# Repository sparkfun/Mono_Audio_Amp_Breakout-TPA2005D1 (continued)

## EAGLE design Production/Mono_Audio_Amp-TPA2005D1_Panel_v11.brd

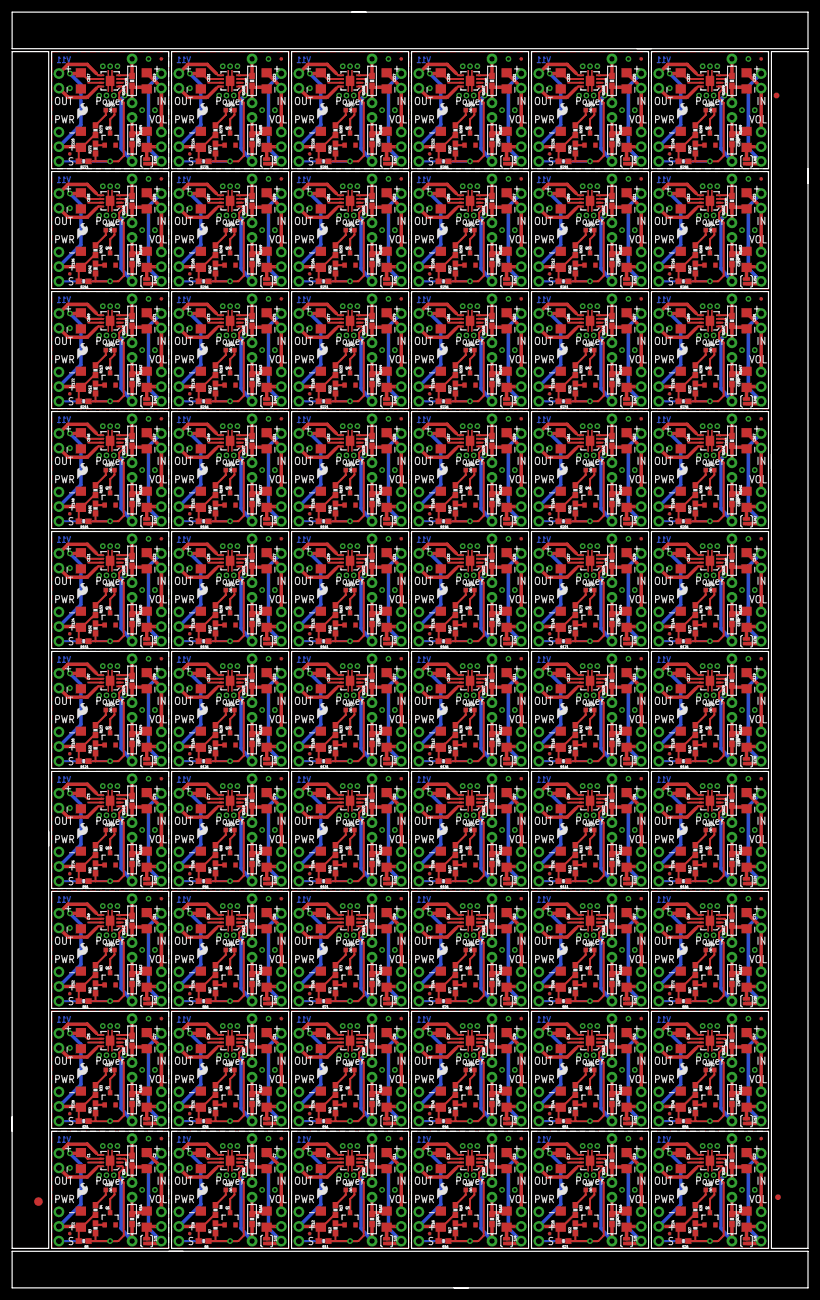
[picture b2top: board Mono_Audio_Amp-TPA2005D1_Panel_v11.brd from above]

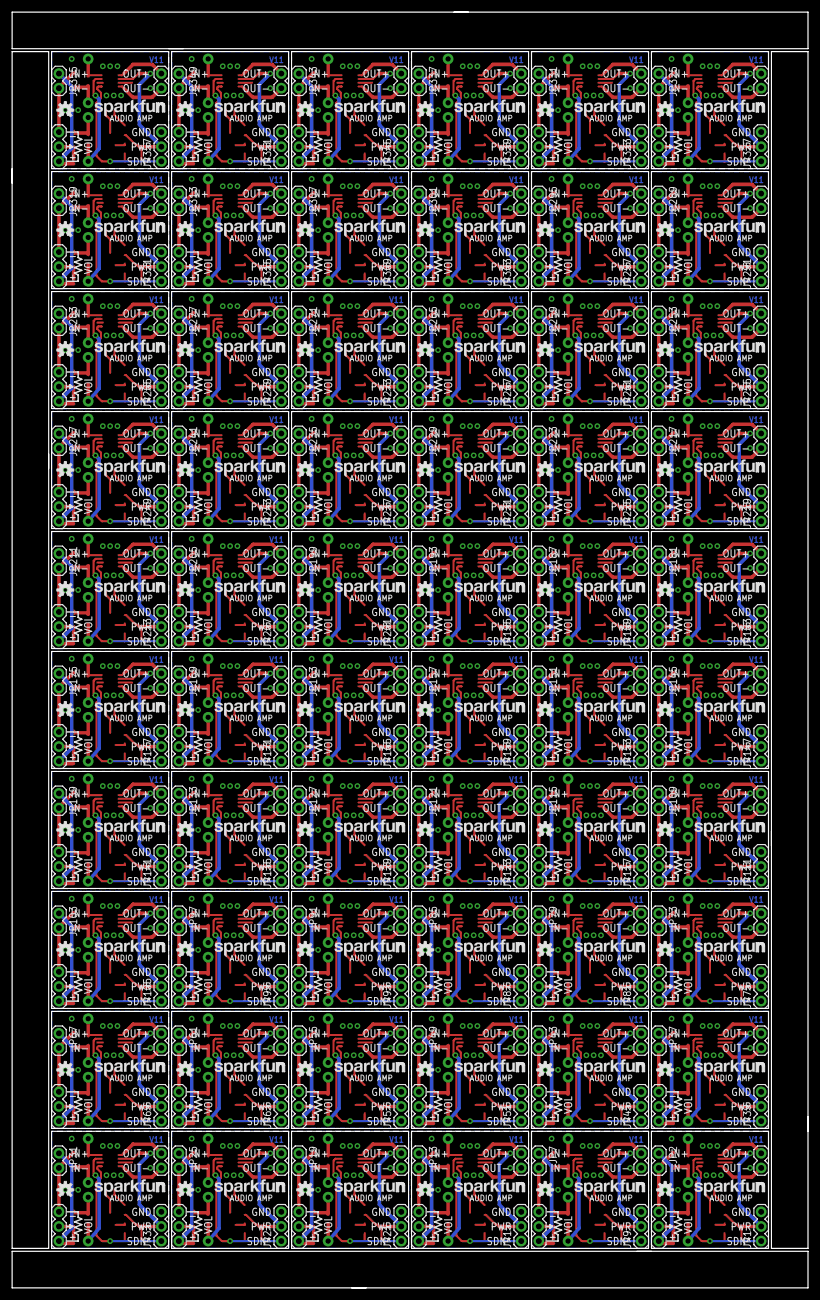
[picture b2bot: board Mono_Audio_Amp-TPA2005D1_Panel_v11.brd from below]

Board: 2 copper layers, 138.2 x 221.5 mm, 1443 parts (360 on the bottom side), 900 nets.

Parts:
C1, C3, C4, C5, C6, C7, C9, C10, C11, C13, C14, C15, C17, C18, C19, C21, C22, C23, C25, C26, C27, C29, C30, C31, C33, C34, C35, C37, C38, C39, C41, C42, C43, C45, C46, C47, C49, C50, C51, C53, C54, C55, C57, C58, C59, C61, C62, C63, C65, C66, C67, C69, C70, C71, C73, C74, C75, C77, C78, C79, C81, C82, C83, C85, C86, C87, C89, C90, C91, C93, C94, C95, C97, C98, C99, C101, C102, C103, C105, C106, C107, C109, C110, C111, C113, C114, C115, C117, C118, C119, C121, C122, C123, C125, C126, C127, C129, C130, C131, C133, C134, C135, C137, C138, C139, C141, C142, C143, C145, C146, C147, C149, C150, C151, C153, C154, C155, C157, C158, C159, C161, C162, C163, C165, C166, C167, C169, C170, C171, C173, C174, C175, C177, C178, C179, C181, C182, C183, C185, C186, C187, C189, C190, C191, C193, C194, C195, C197, C198, C199, C201, C202, C203, C205, C206, C207, C209, C210, C211, C213, C214, C215, C217, C218, C219, C221, C222, C223, C225, C226, C227, C229, C230, C231, C233, C234, C235, C237, C238, C239: 1uF; 1206
C2, C8, C12, C16, C20, C24, C28, C32, C36, C40, C44, C48, C52, C56, C60, C64, C68, C72, C76, C80, C84, C88, C92, C96, C100, C104, C108, C112, C116, C120, C124, C128, C132, C136, C140, C144, C148, C152, C156, C160, C164, C168, C172, C176, C180, C184, C188, C192, C196, C200, C204, C208, C212, C216, C220, C224, C228, C232, C236, C240: 10uF; 1206
E$1: FIDUCIAL-1.5X3
E$2, E$5: FIDUCIAL-1X2
JP1, JP9, JP15, JP21, JP27, JP33, JP39, JP45, JP51, JP57, JP63, JP69, JP75, JP81, JP87, JP93, JP99, JP105, JP111, JP117, JP123, JP129, JP135, JP141, JP147, JP153, JP159, JP165, JP171, JP177, JP183, JP189, JP195, JP201, JP207, JP213, JP219, JP225, JP231, JP237, JP243, JP249, JP255, JP261, JP267, JP273, JP279, JP285, JP291, JP297, JP303, JP309, JP315, JP321, JP327, JP333, JP339, JP345, JP351, JP357: POWER; 1X03
JP2, JP7, JP13, JP19, JP25, JP31, JP37, JP43, JP49, JP55, JP61, JP67, JP73, JP79, JP85, JP91, JP97, JP103, JP109, JP115, JP121, JP127, JP133, JP139, JP145, JP151, JP157, JP163, JP169, JP175, JP181, JP187, JP193, JP199, JP205, JP211, JP217, JP223, JP229, JP235, JP241, JP247, JP253, JP259, JP265, JP271, JP277, JP283, JP289, JP295, JP301, JP307, JP313, JP319, JP325, JP331, JP337, JP343, JP349, JP355: IN; 1X02
JP3, JP8, JP14, JP20, JP26, JP32, JP38, JP44, JP50, JP56, JP62, JP68, JP74, JP80, JP86, JP92, JP98, JP104, JP110, JP116, JP122, JP128, JP134, JP140, JP146, JP152, JP158, JP164, JP170, JP176, JP182, JP188, JP194, JP200, JP206, JP212, JP218, JP224, JP230, JP236, JP242, JP248, JP254, JP260, JP266, JP272, JP278, JP284, JP290, JP296, JP302, JP308, JP314, JP320, JP326, JP332, JP338, JP344, JP350, JP356: OUT; 1X02
JP4, JP10, JP16, JP22, JP28, JP34, JP40, JP46, JP52, JP58, JP64, JP70, JP76, JP82, JP88, JP94, JP100, JP106, JP112, JP118, JP124, JP130, JP136, JP142, JP148, JP154, JP160, JP166, JP172, JP178, JP184, JP190, JP196, JP202, JP208, JP214, JP220, JP226, JP232, JP238, JP244, JP250, JP256, JP262, JP268, JP274, JP280, JP286, JP292, JP298, JP304, JP310, JP316, JP322, JP328, JP334, JP340, JP346, JP352, JP358: VOLUME; 1X03
JP5, JP6, JP11, JP12, JP17, JP18, JP23, JP24, JP29, JP30, JP35, JP36, JP41, JP42, JP47, JP48, JP53, JP54, JP59, JP60, JP65, JP66, JP71, JP72, JP77, JP78, JP83, JP84, JP89, JP90, JP95, JP96, JP101, JP102, JP107, JP108, JP113, JP114, JP119, JP120, JP125, JP126, JP131, JP132, JP137, JP138, JP143, JP144, JP149, JP150, JP155, JP156, JP161, JP162, JP167, JP168, JP173, JP174, JP179, JP180, JP185, JP186, JP191, JP192, JP197, JP198, JP203, JP204, JP209, JP210, JP215, JP216, JP221, JP222, JP227, JP228, JP233, JP234, JP239, JP240, JP245, JP246, JP251, JP252, JP257, JP258, JP263, JP264, JP269, JP270, JP275, JP276, JP281, JP282, JP287, JP288, JP293, JP294, JP299, JP300, JP305, JP306, JP311, JP312, JP317, JP318, JP323, JP324, JP329, JP330, JP335, JP336, JP341, JP342, JP347, JP348, JP353, JP354, JP359, JP360: FIDUCIALUFIDUCIAL; MICRO-FIDUCIAL
LED1, LED2, LED3, LED4, LED5, LED6, LED7, LED8, LED9, LED10, LED11, LED12, LED13, LED14, LED15, LED16, LED17, LED18, LED19, LED20, LED21, LED22, LED23, LED24, LED25, LED26, LED27, LED28, LED29, LED30, LED31, LED32, LED33, LED34, LED35, LED36, LED37, LED38, LED39, LED40, LED41, LED42, LED43, LED44, LED45, LED46, LED47, LED48, LED49, LED50, LED51, LED52, LED53, LED54, LED55, LED56, LED57, LED58, LED59, LED60: LED-0603
LOGO1, LOGO3, LOGO5, LOGO7, LOGO9, LOGO11, LOGO13, LOGO15, LOGO17, LOGO19, LOGO21, LOGO23, LOGO25, LOGO27, LOGO29, LOGO31, LOGO33, LOGO35, LOGO37, LOGO39, LOGO41, LOGO43, LOGO45, LOGO47, LOGO49, LOGO51, LOGO53, LOGO55, LOGO57, LOGO59, LOGO61, LOGO63, LOGO65, LOGO67, LOGO69, LOGO71, LOGO73, LOGO75, LOGO77, LOGO79, LOGO81, LOGO83, LOGO85, LOGO87, LOGO89, LOGO91, LOGO93, LOGO95, LOGO97, LOGO99, LOGO101, LOGO103, LOGO105, LOGO107, LOGO109, LOGO111, LOGO113, LOGO115, LOGO117, LOGO119: LOGO-SFENW2; SFE-NEW-WEB
LOGO2, LOGO4, LOGO6, LOGO8, LOGO10, LOGO12, LOGO14, LOGO16, LOGO18, LOGO20, LOGO22, LOGO24, LOGO26, LOGO28, LOGO30, LOGO32, LOGO34, LOGO36, LOGO38, LOGO40, LOGO42, LOGO44, LOGO46, LOGO48, LOGO50, LOGO52, LOGO54, LOGO56, LOGO58, LOGO60, LOGO62, LOGO64, LOGO66, LOGO68, LOGO70, LOGO72, LOGO74, LOGO76, LOGO78, LOGO80, LOGO82, LOGO84, LOGO86, LOGO88, LOGO90, LOGO92, LOGO94, LOGO96, LOGO98, LOGO100, LOGO102, LOGO104, LOGO106, LOGO108, LOGO110, LOGO112, LOGO114, LOGO116, LOGO118, LOGO120: LOGO-SFESK; SFE-LOGO-FLAME
Q1, Q2, Q3, Q4, Q5, Q6, Q7, Q8, Q9, Q10, Q11, Q12, Q13, Q14, Q15, Q16, Q17, Q18, Q19, Q20, Q21, Q22, Q23, Q24, Q25, Q26, Q27, Q28, Q29, Q30, Q31, Q32, Q33, Q34, Q35, Q36, Q37, Q38, Q39, Q40, Q41, Q42, Q43, Q44, Q45, Q46, Q47, Q48, Q49, Q50, Q51, Q52, Q53, Q54, Q55, Q56, Q57, Q58, Q59, Q60: MMBT2222A; SOT23-3
R1, R2, R9, R10, R14, R15, R19, R20, R24, R25, R29, R30, R34, R35, R39, R40, R44, R45, R49, R50, R54, R55, R59, R60, R64, R65, R69, R70, R74, R75, R79, R80, R84, R85, R89, R90, R94, R95, R99, R100, R104, R105, R109, R110, R114, R115, R119, R120, R124, R125, R129, R130, R134, R135, R139, R140, R144, R145, R149, R150, R154, R155, R159, R160, R164, R165, R169, R170, R174, R175, R179, R180, R184, R185, R189, R190, R194, R195, R199, R200, R204, R205, R209, R210, R214, R215, R219, R220, R224, R225, R229, R230, R234, R235, R239, R240, R244, R245, R249, R250, R254, R255, R259, R260, R264, R265, R269, R270, R274, R275, R279, R280, R284, R285, R289, R290, R294, R295, R299, R300: 150K; 0603-RES
R1A, R1A1, R1A2, R1A3, R1A4, R1A5, R1A6, R1A7, R1A8, R1A9, R1A10, R1A11, R1A12, R1A13, R1A14, R1A15, R1A16, R1A17, R1A18, R1A19, R1A20, R1A21, R1A22, R1A23, R1A24, R1A25, R1A26, R1A27, R1A28, R1A29, R1A30, R1A31, R1A32, R1A33, R1A34, R1A35, R1A36, R1A37, R1A38, R1A39, R1A40, R1A41, R1A42, R1A43, R1A44, R1A45, R1A46, R1A47, R1A48, R1A49, R1A50, R1A51, R1A52, R1A53, R1A54, R1A55, R1A56, R1A57, R1A58, R1A59, R2A, R2A1, R2A2, R2A3, R2A4, R2A5, R2A6, R2A7, R2A8, R2A9, R2A10, R2A11, R2A12, R2A13, R2A14, R2A15, R2A16, R2A17, R2A18, R2A19, R2A20, R2A21, R2A22, R2A23, R2A24, R2A25, R2A26, R2A27, R2A28, R2A29, R2A30, R2A31, R2A32, R2A33, R2A34, R2A35, R2A36, R2A37, R2A38, R2A39, R2A40, R2A41, R2A42, R2A43, R2A44, R2A45, R2A46, R2A47, R2A48, R2A49, R2A50, R2A51, R2A52, R2A53, R2A54, R2A55, R2A56, R2A57, R2A58, R2A59: DNP; AXIAL-0.3
R3, R5, R6, R7, R11, R12, R16, R17, R21, R22, R26, R27, R31, R32, R36, R37, R41, R42, R46, R47, R51, R52, R56, R57, R61, R62, R66, R67, R71, R72, R76, R77, R81, R82, R86, R87, R91, R92, R96, R97, R101, R102, R106, R107, R111, R112, R116, R117, R121, R122, R126, R127, R131, R132, R136, R137, R141, R142, R146, R147, R151, R152, R156, R157, R161, R162, R166, R167, R171, R172, R176, R177, R181, R182, R186, R187, R191, R192, R196, R197, R201, R202, R206, R207, R211, R212, R216, R217, R221, R222, R226, R227, R231, R232, R236, R237, R241, R242, R246, R247, R251, R252, R256, R257, R261, R262, R266, R267, R271, R272, R276, R277, R281, R282, R286, R287, R291, R292, R296, R297: 10K; 0603-RES
R4, R8, R13, R18, R23, R28, R33, R38, R43, R48, R53, R58, R63, R68, R73, R78, R83, R88, R93, R98, R103, R108, R113, R118, R123, R128, R133, R138, R143, R148, R153, R158, R163, R168, R173, R178, R183, R188, R193, R198, R203, R208, R213, R218, R223, R228, R233, R238, R243, R248, R253, R258, R263, R268, R273, R278, R283, R288, R293, R298: 330; 0603-RES
SJ1, SJ2, SJ3, SJ4, SJ5, SJ6, SJ7, SJ8, SJ9, SJ10, SJ11, SJ12, SJ13, SJ14, SJ15, SJ16, SJ17, SJ18, SJ19, SJ20, SJ21, SJ22, SJ23, SJ24, SJ25, SJ26, SJ27, SJ28, SJ29, SJ30, SJ31, SJ32, SJ33, SJ34, SJ35, SJ36, SJ37, SJ38, SJ39, SJ40, SJ41, SJ42, SJ43, SJ44, SJ45, SJ46, SJ47, SJ48, SJ49, SJ50, SJ51, SJ52, SJ53, SJ54, SJ55, SJ56, SJ57, SJ58, SJ59, SJ60: SJ_2S-NOTRACE
U1, U2, U3, U4, U5, U6, U7, U8, U9, U10, U11, U12, U13, U14, U15, U16, U17, U18, U19, U20, U21, U22, U23, U24, U25, U26, U27, U28, U29, U30, U31, U32, U33, U34, U35, U36, U37, U38, U39, U40, U41, U42, U43, U44, U45, U46, U47, U48, U49, U50, U51, U52, U53, U54, U55, U56, U57, U58, U59, U60: TPA2005D1DRB; QFN-8_PAD
U$1, U$2, U$3, U$4, U$5, U$6, U$7, U$8, U$9, U$10, U$11, U$12, U$13, U$14, U$15, U$16, U$17, U$18, U$19, U$20, U$21, U$22, U$23, U$24, U$25, U$26, U$27, U$28, U$29, U$30, U$31, U$32, U$33, U$34, U$35, U$36, U$37, U$38, U$39, U$40, U$41, U$42, U$43, U$44, U$45, U$46, U$47, U$48, U$49, U$50, U$51, U$52, U$53, U$54, U$55, U$56, U$57, U$58, U$59, U$60: OSHW-LOGOS; OSHW-LOGO-S

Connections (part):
GND: C1.2, C2.2, JP1.3, Q1.2, U1.7, U1.10, U1.11, U1.12, U1.13
GND1: C5.2, C8.2, JP9.3, Q2.2, U2.7, U2.10, U2.11, U2.12, U2.13
GND2: C9.2, C12.2, JP15.3, Q3.2, U3.7, U3.10, U3.11, U3.12, U3.13
GND3: C13.2, C16.2, JP21.3, Q4.2, U4.7, U4.10, U4.11, U4.12, U4.13
GND4: C17.2, C20.2, JP27.3, Q5.2, U5.7, U5.10, U5.11, U5.12, U5.13
GND5: C21.2, C24.2, JP33.3, Q6.2, U6.7, U6.10, U6.11, U6.12, U6.13
GND6: C25.2, C28.2, JP39.3, Q7.2, U7.7, U7.10, U7.11, U7.12, U7.13
GND7: C29.2, C32.2, JP45.3, Q8.2, U8.7, U8.10, U8.11, U8.12, U8.13
GND8: C33.2, C36.2, JP51.3, Q9.2, U9.7, U9.10, U9.11, U9.12, U9.13
GND9: C37.2, C40.2, JP57.3, Q10.2, U10.7, U10.10, U10.11, U10.12, U10.13
GND10: C41.2, C44.2, JP63.3, Q11.2, U11.7, U11.10, U11.11, U11.12, U11.13
GND11: C45.2, C48.2, JP69.3, Q12.2, U12.7, U12.10, U12.11, U12.12, U12.13
GND12: C49.2, C52.2, JP75.3, Q13.2, U13.7, U13.10, U13.11, U13.12, U13.13
GND13: C53.2, C56.2, JP81.3, Q14.2, U14.7, U14.10, U14.11, U14.12, U14.13
GND14: C57.2, C60.2, JP87.3, Q15.2, U15.7, U15.10, U15.11, U15.12, U15.13
GND15: C61.2, C64.2, JP93.3, Q16.2, U16.7, U16.10, U16.11, U16.12, U16.13
GND16: C65.2, C68.2, JP99.3, Q17.2, U17.7, U17.10, U17.11, U17.12, U17.13
GND17: C69.2, C72.2, JP105.3, Q18.2, U18.7, U18.10, U18.11, U18.12, U18.13
GND18: C73.2, C76.2, JP111.3, Q19.2, U19.7, U19.10, U19.11, U19.12, U19.13
GND19: C77.2, C80.2, JP117.3, Q20.2, U20.7, U20.10, U20.11, U20.12, U20.13
GND20: C81.2, C84.2, JP123.3, Q21.2, U21.7, U21.10, U21.11, U21.12, U21.13
GND21: C85.2, C88.2, JP129.3, Q22.2, U22.7, U22.10, U22.11, U22.12, U22.13
GND22: C89.2, C92.2, JP135.3, Q23.2, U23.7, U23.10, U23.11, U23.12, U23.13
GND23: C93.2, C96.2, JP141.3, Q24.2, U24.7, U24.10, U24.11, U24.12, U24.13
GND24: C97.2, C100.2, JP147.3, Q25.2, U25.7, U25.10, U25.11, U25.12, U25.13
GND25: C101.2, C104.2, JP153.3, Q26.2, U26.7, U26.10, U26.11, U26.12, U26.13
GND26: C105.2, C108.2, JP159.3, Q27.2, U27.7, U27.10, U27.11, U27.12, U27.13
GND27: C109.2, C112.2, JP165.3, Q28.2, U28.7, U28.10, U28.11, U28.12, U28.13
GND28: C113.2, C116.2, JP171.3, Q29.2, U29.7, U29.10, U29.11, U29.12, U29.13
GND29: C117.2, C120.2, JP177.3, Q30.2, U30.7, U30.10, U30.11, U30.12, U30.13
GND30: C121.2, C124.2, JP183.3, Q31.2, U31.7, U31.10, U31.11, U31.12, U31.13
GND31: C125.2, C128.2, JP189.3, Q32.2, U32.7, U32.10, U32.11, U32.12, U32.13
GND32: C129.2, C132.2, JP195.3, Q33.2, U33.7, U33.10, U33.11, U33.12, U33.13
GND33: C133.2, C136.2, JP201.3, Q34.2, U34.7, U34.10, U34.11, U34.12, U34.13
GND34: C137.2, C140.2, JP207.3, Q35.2, U35.7, U35.10, U35.11, U35.12, U35.13
GND35: C141.2, C144.2, JP213.3, Q36.2, U36.7, U36.10, U36.11, U36.12, U36.13
GND36: C145.2, C148.2, JP219.3, Q37.2, U37.7, U37.10, U37.11, U37.12, U37.13
GND37: C149.2, C152.2, JP225.3, Q38.2, U38.7, U38.10, U38.11, U38.12, U38.13
GND38: C153.2, C156.2, JP231.3, Q39.2, U39.7, U39.10, U39.11, U39.12, U39.13
GND39: C157.2, C160.2, JP237.3, Q40.2, U40.7, U40.10, U40.11, U40.12, U40.13
GND40: C161.2, C164.2, JP243.3, Q41.2, U41.7, U41.10, U41.11, U41.12, U41.13
GND41: C165.2, C168.2, JP249.3, Q42.2, U42.7, U42.10, U42.11, U42.12, U42.13
GND42: C169.2, C172.2, JP255.3, Q43.2, U43.7, U43.10, U43.11, U43.12, U43.13
GND43: C173.2, C176.2, JP261.3, Q44.2, U44.7, U44.10, U44.11, U44.12, U44.13
GND44: C177.2, C180.2, JP267.3, Q45.2, U45.7, U45.10, U45.11, U45.12, U45.13
GND45: C181.2, C184.2, JP273.3, Q46.2, U46.7, U46.10, U46.11, U46.12, U46.13
GND46: C185.2, C188.2, JP279.3, Q47.2, U47.7, U47.10, U47.11, U47.12, U47.13
GND47: C189.2, C192.2, JP285.3, Q48.2, U48.7, U48.10, U48.11, U48.12, U48.13
GND48: C193.2, C196.2, JP291.3, Q49.2, U49.7, U49.10, U49.11, U49.12, U49.13
GND49: C197.2, C200.2, JP297.3, Q50.2, U50.7, U50.10, U50.11, U50.12, U50.13
GND50: C201.2, C204.2, JP303.3, Q51.2, U51.7, U51.10, U51.11, U51.12, U51.13
GND51: C205.2, C208.2, JP309.3, Q52.2, U52.7, U52.10, U52.11, U52.12, U52.13
GND52: C209.2, C212.2, JP315.3, Q53.2, U53.7, U53.10, U53.11, U53.12, U53.13
GND53: C213.2, C216.2, JP321.3, Q54.2, U54.7, U54.10, U54.11, U54.12, U54.13
GND54: C217.2, C220.2, JP327.3, Q55.2, U55.7, U55.10, U55.11, U55.12, U55.13
GND55: C221.2, C224.2, JP333.3, Q56.2, U56.7, U56.10, U56.11, U56.12, U56.13
GND56: C225.2, C228.2, JP339.3, Q57.2, U57.7, U57.10, U57.11, U57.12, U57.13
GND57: C229.2, C232.2, JP345.3, Q58.2, U58.7, U58.10, U58.11, U58.12, U58.13
GND58: C233.2, C236.2, JP351.3, Q59.2, U59.7, U59.10, U59.11, U59.12, U59.13
GND59: C237.2, C240.2, JP357.3, Q60.2, U60.7, U60.10, U60.11, U60.12, U60.13
IN+: JP2.1, JP4.1, SJ1.2
IN+1: JP7.1, JP10.1, SJ2.2
IN+2: JP13.1, JP16.1, SJ3.2
IN+3: JP19.1, JP22.1, SJ4.2
IN+4: JP25.1, JP28.1, SJ5.2
IN+5: JP31.1, JP34.1, SJ6.2
IN+6: JP37.1, JP40.1, SJ7.2
IN+7: JP43.1, JP46.1, SJ8.2
IN+8: JP49.1, JP52.1, SJ9.2
IN+9: JP55.1, JP58.1, SJ10.2
IN+10: JP61.1, JP64.1, SJ11.2
IN+11: JP67.1, JP70.1, SJ12.2
IN+12: JP73.1, JP76.1, SJ13.2
IN+13: JP79.1, JP82.1, SJ14.2
IN+14: JP85.1, JP88.1, SJ15.2
IN+15: JP91.1, JP94.1, SJ16.2
IN+16: JP97.1, JP100.1, SJ17.2
IN+17: JP103.1, JP106.1, SJ18.2
IN+18: JP109.1, JP112.1, SJ19.2
IN+19: JP115.1, JP118.1, SJ20.2
IN+20: JP121.1, JP124.1, SJ21.2
IN+21: JP127.1, JP130.1, SJ22.2
IN+22: JP133.1, JP136.1, SJ23.2
IN+23: JP139.1, JP142.1, SJ24.2
IN+24: JP145.1, JP148.1, SJ25.2
IN+25: JP151.1, JP154.1, SJ26.2
IN+26: JP157.1, JP160.1, SJ27.2
IN+27: JP163.1, JP166.1, SJ28.2
IN+28: JP169.1, JP172.1, SJ29.2
IN+29: JP175.1, JP178.1, SJ30.2
IN+30: JP181.1, JP184.1, SJ31.2
IN+31: JP187.1, JP190.1, SJ32.2
IN+32: JP193.1, JP196.1, SJ33.2
IN+33: JP199.1, JP202.1, SJ34.2
IN+34: JP205.1, JP208.1, SJ35.2
IN+35: JP211.1, JP214.1, SJ36.2
IN+36: JP217.1, JP220.1, SJ37.2
IN+37: JP223.1, JP226.1, SJ38.2
IN+38: JP229.1, JP232.1, SJ39.2
IN+39: JP235.1, JP238.1, SJ40.2
IN+40: JP241.1, JP244.1, SJ41.2
IN+41: JP247.1, JP250.1, SJ42.2
IN+42: JP253.1, JP256.1, SJ43.2
IN+43: JP259.1, JP262.1, SJ44.2
IN+44: JP265.1, JP268.1, SJ45.2
IN+45: JP271.1, JP274.1, SJ46.2
IN+46: JP277.1, JP280.1, SJ47.2
IN+47: JP283.1, JP286.1, SJ48.2
IN+48: JP289.1, JP292.1, SJ49.2
IN+49: JP295.1, JP298.1, SJ50.2
IN+50: JP301.1, JP304.1, SJ51.2
IN+51: JP307.1, JP310.1, SJ52.2
IN+52: JP313.1, JP316.1, SJ53.2
IN+53: JP319.1, JP322.1, SJ54.2
IN+54: JP325.1, JP328.1, SJ55.2
IN+55: JP331.1, JP334.1, SJ56.2
IN+56: JP337.1, JP340.1, SJ57.2
IN+57: JP343.1, JP346.1, SJ58.2
IN+58: JP349.1, JP352.1, SJ59.2
IN+59: JP355.1, JP358.1, SJ60.2
IN+AMP: R1.2, R1A.P$2, U1.3
IN+AMP1: R1A1.P$2, R9.2, U2.3
IN+AMP2: R1A2.P$2, R14.2, U3.3
IN+AMP3: R1A3.P$2, R19.2, U4.3
IN+AMP4: R1A4.P$2, R24.2, U5.3
IN+AMP5: R1A5.P$2, R29.2, U6.3
IN+AMP6: R1A6.P$2, R34.2, U7.3
IN+AMP7: R1A7.P$2, R39.2, U8.3
IN+AMP8: R1A8.P$2, R44.2, U9.3
IN+AMP9: R1A9.P$2, R49.2, U10.3
IN+AMP10: R1A10.P$2, R54.2, U11.3
IN+AMP11: R1A11.P$2, R59.2, U12.3
IN+AMP12: R1A12.P$2, R64.2, U13.3
IN+AMP13: R1A13.P$2, R69.2, U14.3
IN+AMP14: R1A14.P$2, R74.2, U15.3
IN+AMP15: R1A15.P$2, R79.2, U16.3
IN+AMP16: R1A16.P$2, R84.2, U17.3
IN+AMP17: R1A17.P$2, R89.2, U18.3
IN+AMP18: R1A18.P$2, R94.2, U19.3
IN+AMP19: R1A19.P$2, R99.2, U20.3
IN+AMP20: R1A20.P$2, R104.2, U21.3
IN+AMP21: R1A21.P$2, R109.2, U22.3
IN+AMP22: R1A22.P$2, R114.2, U23.3
IN+AMP23: R1A23.P$2, R119.2, U24.3
IN+AMP24: R1A24.P$2, R124.2, U25.3
IN+AMP25: R1A25.P$2, R129.2, U26.3
IN+AMP26: R1A26.P$2, R134.2, U27.3
IN+AMP27: R1A27.P$2, R139.2, U28.3
IN+AMP28: R1A28.P$2, R144.2, U29.3
IN+AMP29: R1A29.P$2, R149.2, U30.3
IN+AMP30: R1A30.P$2, R154.2, U31.3
IN+AMP31: R1A31.P$2, R159.2, U32.3
IN+AMP32: R1A32.P$2, R164.2, U33.3
IN+AMP33: R1A33.P$2, R169.2, U34.3
IN+AMP34: R1A34.P$2, R174.2, U35.3
IN+AMP35: R1A35.P$2, R179.2, U36.3
IN+AMP36: R1A36.P$2, R184.2, U37.3
IN+AMP37: R1A37.P$2, R189.2, U38.3
IN+AMP38: R1A38.P$2, R194.2, U39.3
IN+AMP39: R1A39.P$2, R199.2, U40.3
IN+AMP40: R1A40.P$2, R204.2, U41.3
IN+AMP41: R1A41.P$2, R209.2, U42.3
IN+AMP42: R1A42.P$2, R214.2, U43.3
IN+AMP43: R1A43.P$2, R219.2, U44.3
IN+AMP44: R1A44.P$2, R224.2, U45.3
IN+AMP45: R1A45.P$2, R229.2, U46.3
IN+AMP46: R1A46.P$2, R234.2, U47.3
IN+AMP47: R1A47.P$2, R239.2, U48.3
IN+AMP48: R1A48.P$2, R244.2, U49.3
IN+AMP49: R1A49.P$2, R249.2, U50.3
IN+AMP50: R1A50.P$2, R254.2, U51.3
IN+AMP51: R1A51.P$2, R259.2, U52.3
IN+AMP52: R1A52.P$2, R264.2, U53.3
IN+AMP53: R1A53.P$2, R269.2, U54.3
IN+AMP54: R1A54.P$2, R274.2, U55.3
IN+AMP55: R1A55.P$2, R279.2, U56.3
IN+AMP56: R1A56.P$2, R284.2, U57.3
IN+AMP57: R1A57.P$2, R289.2, U58.3
IN+AMP58: R1A58.P$2, R294.2, U59.3
IN+AMP59: R1A59.P$2, R299.2, U60.3
IN-: C3.1, JP2.2, JP4.3
IN-1: C7.1, JP7.2, JP10.3
IN-2: C11.1, JP13.2, JP16.3
IN-3: C15.1, JP19.2, JP22.3
IN-4: C19.1, JP25.2, JP28.3
IN-5: C23.1, JP31.2, JP34.3
IN-6: C27.1, JP37.2, JP40.3
IN-7: C31.1, JP43.2, JP46.3
IN-8: C35.1, JP49.2, JP52.3
IN-9: C39.1, JP55.2, JP58.3
IN-10: C43.1, JP61.2, JP64.3
IN-11: C47.1, JP67.2, JP70.3
IN-12: C51.1, JP73.2, JP76.3
IN-13: C55.1, JP79.2, JP82.3
IN-14: C59.1, JP85.2, JP88.3
IN-15: C63.1, JP91.2, JP94.3
IN-16: C67.1, JP97.2, JP100.3
IN-17: C71.1, JP103.2, JP106.3
IN-18: C75.1, JP109.2, JP112.3
IN-19: C79.1, JP115.2, JP118.3
IN-20: C83.1, JP121.2, JP124.3
IN-21: C87.1, JP127.2, JP130.3
IN-22: C91.1, JP133.2, JP136.3
IN-23: C95.1, JP139.2, JP142.3
IN-24: C99.1, JP145.2, JP148.3
IN-25: C103.1, JP151.2, JP154.3
IN-26: C107.1, JP157.2, JP160.3
IN-27: C111.1, JP163.2, JP166.3
IN-28: C115.1, JP169.2, JP172.3
IN-29: C119.1, JP175.2, JP178.3
IN-30: C123.1, JP181.2, JP184.3
IN-31: C127.1, JP187.2, JP190.3
IN-32: C131.1, JP193.2, JP196.3
IN-33: C135.1, JP199.2, JP202.3
IN-34: C139.1, JP205.2, JP208.3
IN-35: C143.1, JP211.2, JP214.3
IN-36: C147.1, JP217.2, JP220.3
IN-37: C151.1, JP223.2, JP226.3
IN-38: C155.1, JP229.2, JP232.3
IN-39: C159.1, JP235.2, JP238.3
IN-40: C163.1, JP241.2, JP244.3
IN-41: C167.1, JP247.2, JP250.3
IN-42: C171.1, JP253.2, JP256.3
IN-43: C175.1, JP259.2, JP262.3
IN-44: C179.1, JP265.2, JP268.3
IN-45: C183.1, JP271.2, JP274.3
IN-46: C187.1, JP277.2, JP280.3
IN-47: C191.1, JP283.2, JP286.3
IN-48: C195.1, JP289.2, JP292.3
IN-49: C199.1, JP295.2, JP298.3
IN-50: C203.1, JP301.2, JP304.3
IN-51: C207.1, JP307.2, JP310.3
IN-52: C211.1, JP313.2, JP316.3
IN-53: C215.1, JP319.2, JP322.3
IN-54: C219.1, JP325.2, JP328.3
IN-55: C223.1, JP331.2, JP334.3
IN-56: C227.1, JP337.2, JP340.3
IN-57: C231.1, JP343.2, JP346.3
IN-58: C235.1, JP349.2, JP352.3
IN-59: C239.1, JP355.2, JP358.3
IN-AMP: R2.2, R2A.P$2, U1.4
IN-AMP1: R2A1.P$2, R10.2, U2.4
IN-AMP2: R2A2.P$2, R15.2, U3.4
IN-AMP3: R2A3.P$2, R20.2, U4.4
IN-AMP4: R2A4.P$2, R25.2, U5.4
IN-AMP5: R2A5.P$2, R30.2, U6.4
IN-AMP6: R2A6.P$2, R35.2, U7.4
IN-AMP7: R2A7.P$2, R40.2, U8.4
IN-AMP8: R2A8.P$2, R45.2, U9.4
IN-AMP9: R2A9.P$2, R50.2, U10.4
IN-AMP10: R2A10.P$2, R55.2, U11.4
IN-AMP11: R2A11.P$2, R60.2, U12.4
IN-AMP12: R2A12.P$2, R65.2, U13.4
IN-AMP13: R2A13.P$2, R70.2, U14.4
IN-AMP14: R2A14.P$2, R75.2, U15.4
IN-AMP15: R2A15.P$2, R80.2, U16.4
IN-AMP16: R2A16.P$2, R85.2, U17.4
IN-AMP17: R2A17.P$2, R90.2, U18.4
IN-AMP18: R2A18.P$2, R95.2, U19.4
IN-AMP19: R2A19.P$2, R100.2, U20.4
IN-AMP20: R2A20.P$2, R105.2, U21.4
IN-AMP21: R2A21.P$2, R110.2, U22.4
IN-AMP22: R2A22.P$2, R115.2, U23.4
IN-AMP23: R2A23.P$2, R120.2, U24.4
IN-AMP24: R2A24.P$2, R125.2, U25.4
IN-AMP25: R2A25.P$2, R130.2, U26.4
IN-AMP26: R2A26.P$2, R135.2, U27.4
IN-AMP27: R2A27.P$2, R140.2, U28.4
IN-AMP28: R2A28.P$2, R145.2, U29.4
IN-AMP29: R2A29.P$2, R150.2, U30.4
IN-AMP30: R2A30.P$2, R155.2, U31.4
IN-AMP31: R2A31.P$2, R160.2, U32.4
IN-AMP32: R2A32.P$2, R165.2, U33.4
IN-AMP33: R2A33.P$2, R170.2, U34.4
IN-AMP34: R2A34.P$2, R175.2, U35.4
IN-AMP35: R2A35.P$2, R180.2, U36.4
IN-AMP36: R2A36.P$2, R185.2, U37.4
IN-AMP37: R2A37.P$2, R190.2, U38.4
IN-AMP38: R2A38.P$2, R195.2, U39.4
IN-AMP39: R2A39.P$2, R200.2, U40.4
IN-AMP40: R2A40.P$2, R205.2, U41.4
IN-AMP41: R2A41.P$2, R210.2, U42.4
IN-AMP42: R2A42.P$2, R215.2, U43.4
IN-AMP43: R2A43.P$2, R220.2, U44.4
IN-AMP44: R2A44.P$2, R225.2, U45.4
IN-AMP45: R2A45.P$2, R230.2, U46.4
IN-AMP46: R2A46.P$2, R235.2, U47.4
IN-AMP47: R2A47.P$2, R240.2, U48.4
IN-AMP48: R2A48.P$2, R245.2, U49.4
IN-AMP49: R2A49.P$2, R250.2, U50.4
IN-AMP50: R2A50.P$2, R255.2, U51.4
IN-AMP51: R2A51.P$2, R260.2, U52.4
IN-AMP52: R2A52.P$2, R265.2, U53.4
IN-AMP53: R2A53.P$2, R270.2, U54.4
IN-AMP54: R2A54.P$2, R275.2, U55.4
IN-AMP55: R2A55.P$2, R280.2, U56.4
IN-AMP56: R2A56.P$2, R285.2, U57.4
IN-AMP57: R2A57.P$2, R290.2, U58.4
IN-AMP58: R2A58.P$2, R295.2, U59.4
IN-AMP59: R2A59.P$2, R300.2, U60.4
unnamed: C4.1, JP4.2, SJ1.1
unnamed: C4.2, R1.1, R1A.P$1
unnamed: C3.2, R2.1, R2A.P$1
unnamed: C6.1, JP10.2, SJ2.1
unnamed: LED2.A, R8.1
unnamed: Q2.1, R7.2
unnamed: LED1.C, Q1.3
unnamed: LED1.A, R4.1
unnamed: Q1.1, R3.2
unnamed: LED2.C, Q2.3
unnamed: C6.2, R1A1.P$1, R9.1
unnamed: C7.2, R2A1.P$1, R10.1
unnamed: C10.1, JP16.2, SJ3.1
unnamed: LED3.A, R13.1
unnamed: Q3.1, R12.2
unnamed: LED3.C, Q3.3
unnamed: C10.2, R1A2.P$1, R14.1
unnamed: C11.2, R2A2.P$1, R15.1
unnamed: C14.1, JP22.2, SJ4.1
unnamed: LED4.A, R18.1
unnamed: Q4.1, R17.2
unnamed: LED4.C, Q4.3
unnamed: C14.2, R1A3.P$1, R19.1
unnamed: C15.2, R2A3.P$1, R20.1
unnamed: C18.1, JP28.2, SJ5.1
unnamed: LED5.A, R23.1
unnamed: Q5.1, R22.2
unnamed: LED5.C, Q5.3
unnamed: C18.2, R1A4.P$1, R24.1
unnamed: C19.2, R2A4.P$1, R25.1
unnamed: C22.1, JP34.2, SJ6.1
unnamed: LED6.A, R28.1
unnamed: Q6.1, R27.2
unnamed: LED6.C, Q6.3
unnamed: C22.2, R1A5.P$1, R29.1
unnamed: C23.2, R2A5.P$1, R30.1
unnamed: C26.1, JP40.2, SJ7.1
unnamed: LED7.A, R33.1
unnamed: Q7.1, R32.2
unnamed: LED7.C, Q7.3
unnamed: C26.2, R1A6.P$1, R34.1
unnamed: C27.2, R2A6.P$1, R35.1
unnamed: C30.1, JP46.2, SJ8.1
unnamed: LED8.A, R38.1
unnamed: Q8.1, R37.2
unnamed: LED8.C, Q8.3
unnamed: C30.2, R1A7.P$1, R39.1
unnamed: C31.2, R2A7.P$1, R40.1
unnamed: C34.1, JP52.2, SJ9.1
unnamed: LED9.A, R43.1
unnamed: Q9.1, R42.2
unnamed: LED9.C, Q9.3
unnamed: C34.2, R1A8.P$1, R44.1
unnamed: C35.2, R2A8.P$1, R45.1
unnamed: C38.1, JP58.2, SJ10.1
unnamed: LED10.A, R48.1
unnamed: Q10.1, R47.2
unnamed: LED10.C, Q10.3
unnamed: C38.2, R1A9.P$1, R49.1
unnamed: C39.2, R2A9.P$1, R50.1
unnamed: C42.1, JP64.2, SJ11.1
unnamed: LED11.A, R53.1
unnamed: Q11.1, R52.2
unnamed: LED11.C, Q11.3
unnamed: C42.2, R1A10.P$1, R54.1
unnamed: C43.2, R2A10.P$1, R55.1
unnamed: C46.1, JP70.2, SJ12.1
unnamed: LED12.A, R58.1
unnamed: Q12.1, R57.2
unnamed: LED12.C, Q12.3
unnamed: C46.2, R1A11.P$1, R59.1
unnamed: C47.2, R2A11.P$1, R60.1
unnamed: C50.1, JP76.2, SJ13.1
unnamed: LED13.A, R63.1
unnamed: Q13.1, R62.2
unnamed: LED13.C, Q13.3
unnamed: C50.2, R1A12.P$1, R64.1
unnamed: C51.2, R2A12.P$1, R65.1
unnamed: C54.1, JP82.2, SJ14.1
unnamed: LED14.A, R68.1
unnamed: Q14.1, R67.2
unnamed: LED14.C, Q14.3
unnamed: C54.2, R1A13.P$1, R69.1
unnamed: C55.2, R2A13.P$1, R70.1
unnamed: C58.1, JP88.2, SJ15.1
unnamed: LED15.A, R73.1
unnamed: Q15.1, R72.2
unnamed: LED15.C, Q15.3
unnamed: C58.2, R1A14.P$1, R74.1
unnamed: C59.2, R2A14.P$1, R75.1
unnamed: C62.1, JP94.2, SJ16.1
unnamed: LED16.A, R78.1
unnamed: Q16.1, R77.2
unnamed: LED16.C, Q16.3
unnamed: C62.2, R1A15.P$1, R79.1
unnamed: C63.2, R2A15.P$1, R80.1
unnamed: C66.1, JP100.2, SJ17.1
unnamed: LED17.A, R83.1
unnamed: Q17.1, R82.2
unnamed: LED17.C, Q17.3
unnamed: C66.2, R1A16.P$1, R84.1
unnamed: C67.2, R2A16.P$1, R85.1
unnamed: C70.1, JP106.2, SJ18.1
unnamed: LED18.A, R88.1
unnamed: Q18.1, R87.2
unnamed: LED18.C, Q18.3
unnamed: C70.2, R1A17.P$1, R89.1
unnamed: C71.2, R2A17.P$1, R90.1
unnamed: C74.1, JP112.2, SJ19.1
unnamed: LED19.A, R93.1
unnamed: Q19.1, R92.2
unnamed: LED19.C, Q19.3
unnamed: C74.2, R1A18.P$1, R94.1
unnamed: C75.2, R2A18.P$1, R95.1
unnamed: C78.1, JP118.2, SJ20.1
unnamed: LED20.A, R98.1
unnamed: Q20.1, R97.2
unnamed: LED20.C, Q20.3
unnamed: C78.2, R1A19.P$1, R99.1
unnamed: C79.2, R2A19.P$1, R100.1
unnamed: C82.1, JP124.2, SJ21.1
unnamed: LED21.A, R103.1
unnamed: Q21.1, R102.2
unnamed: LED21.C, Q21.3
unnamed: C82.2, R1A20.P$1, R104.1
unnamed: C83.2, R2A20.P$1, R105.1
unnamed: C86.1, JP130.2, SJ22.1
unnamed: LED22.A, R108.1
unnamed: Q22.1, R107.2
unnamed: LED22.C, Q22.3
unnamed: C86.2, R1A21.P$1, R109.1
unnamed: C87.2, R2A21.P$1, R110.1
unnamed: C90.1, JP136.2, SJ23.1
unnamed: LED23.A, R113.1
unnamed: Q23.1, R112.2
unnamed: LED23.C, Q23.3
unnamed: C90.2, R1A22.P$1, R114.1
unnamed: C91.2, R2A22.P$1, R115.1
unnamed: C94.1, JP142.2, SJ24.1
unnamed: LED24.A, R118.1
unnamed: Q24.1, R117.2
unnamed: LED24.C, Q24.3
unnamed: C94.2, R1A23.P$1, R119.1
unnamed: C95.2, R2A23.P$1, R120.1
unnamed: C98.1, JP148.2, SJ25.1
unnamed: LED25.A, R123.1
unnamed: Q25.1, R122.2
unnamed: LED25.C, Q25.3
unnamed: C98.2, R1A24.P$1, R124.1
unnamed: C99.2, R2A24.P$1, R125.1
unnamed: C102.1, JP154.2, SJ26.1
unnamed: LED26.A, R128.1
unnamed: Q26.1, R127.2
unnamed: LED26.C, Q26.3
unnamed: C102.2, R1A25.P$1, R129.1
unnamed: C103.2, R2A25.P$1, R130.1
unnamed: C106.1, JP160.2, SJ27.1
unnamed: LED27.A, R133.1
unnamed: Q27.1, R132.2
unnamed: LED27.C, Q27.3
unnamed: C106.2, R1A26.P$1, R134.1
unnamed: C107.2, R2A26.P$1, R135.1
unnamed: C110.1, JP166.2, SJ28.1
unnamed: LED28.A, R138.1
unnamed: Q28.1, R137.2
unnamed: LED28.C, Q28.3
unnamed: C110.2, R1A27.P$1, R139.1
unnamed: C111.2, R2A27.P$1, R140.1
unnamed: C114.1, JP172.2, SJ29.1
unnamed: LED29.A, R143.1
unnamed: Q29.1, R142.2
unnamed: LED29.C, Q29.3
unnamed: C114.2, R1A28.P$1, R144.1
unnamed: C115.2, R2A28.P$1, R145.1
unnamed: C118.1, JP178.2, SJ30.1
unnamed: LED30.A, R148.1
unnamed: Q30.1, R147.2
unnamed: LED30.C, Q30.3
unnamed: C118.2, R1A29.P$1, R149.1
unnamed: C119.2, R2A29.P$1, R150.1
unnamed: C122.1, JP184.2, SJ31.1
unnamed: LED31.A, R153.1
unnamed: Q31.1, R152.2
unnamed: LED31.C, Q31.3
unnamed: C122.2, R1A30.P$1, R154.1
unnamed: C123.2, R2A30.P$1, R155.1
unnamed: C126.1, JP190.2, SJ32.1
unnamed: LED32.A, R158.1
unnamed: Q32.1, R157.2
unnamed: LED32.C, Q32.3
unnamed: C126.2, R1A31.P$1, R159.1
unnamed: C127.2, R2A31.P$1, R160.1
unnamed: C130.1, JP196.2, SJ33.1
unnamed: LED33.A, R163.1
unnamed: Q33.1, R162.2
unnamed: LED33.C, Q33.3
unnamed: C130.2, R1A32.P$1, R164.1
unnamed: C131.2, R2A32.P$1, R165.1
unnamed: C134.1, JP202.2, SJ34.1
unnamed: LED34.A, R168.1
unnamed: Q34.1, R167.2
unnamed: LED34.C, Q34.3
unnamed: C134.2, R1A33.P$1, R169.1
unnamed: C135.2, R2A33.P$1, R170.1
unnamed: C138.1, JP208.2, SJ35.1
unnamed: LED35.A, R173.1
unnamed: Q35.1, R172.2
unnamed: LED35.C, Q35.3
unnamed: C138.2, R1A34.P$1, R174.1
unnamed: C139.2, R2A34.P$1, R175.1
unnamed: C142.1, JP214.2, SJ36.1
unnamed: LED36.A, R178.1
unnamed: Q36.1, R177.2
unnamed: LED36.C, Q36.3
unnamed: C142.2, R1A35.P$1, R179.1
unnamed: C143.2, R2A35.P$1, R180.1
unnamed: C146.1, JP220.2, SJ37.1
unnamed: LED37.A, R183.1
unnamed: Q37.1, R182.2
unnamed: LED37.C, Q37.3
unnamed: C146.2, R1A36.P$1, R184.1
unnamed: C147.2, R2A36.P$1, R185.1
unnamed: C150.1, JP226.2, SJ38.1
unnamed: LED38.A, R188.1
unnamed: Q38.1, R187.2
unnamed: LED38.C, Q38.3
unnamed: C150.2, R1A37.P$1, R189.1
unnamed: C151.2, R2A37.P$1, R190.1
unnamed: C154.1, JP232.2, SJ39.1
unnamed: LED39.A, R193.1
unnamed: Q39.1, R192.2
unnamed: LED39.C, Q39.3
unnamed: C154.2, R1A38.P$1, R194.1
unnamed: C155.2, R2A38.P$1, R195.1
unnamed: C158.1, JP238.2, SJ40.1
unnamed: LED40.A, R198.1
unnamed: Q40.1, R197.2
unnamed: LED40.C, Q40.3
unnamed: C158.2, R1A39.P$1, R199.1
unnamed: C159.2, R2A39.P$1, R200.1
unnamed: C162.1, JP244.2, SJ41.1
unnamed: LED41.A, R203.1
unnamed: Q41.1, R202.2
unnamed: LED41.C, Q41.3
unnamed: C162.2, R1A40.P$1, R204.1
unnamed: C163.2, R2A40.P$1, R205.1
unnamed: C166.1, JP250.2, SJ42.1
unnamed: LED42.A, R208.1
unnamed: Q42.1, R207.2
unnamed: LED42.C, Q42.3
unnamed: C166.2, R1A41.P$1, R209.1
unnamed: C167.2, R2A41.P$1, R210.1
unnamed: C170.1, JP256.2, SJ43.1
unnamed: LED43.A, R213.1
unnamed: Q43.1, R212.2
unnamed: LED43.C, Q43.3
unnamed: C170.2, R1A42.P$1, R214.1
unnamed: C171.2, R2A42.P$1, R215.1
unnamed: C174.1, JP262.2, SJ44.1
unnamed: LED44.A, R218.1
unnamed: Q44.1, R217.2
unnamed: LED44.C, Q44.3
unnamed: C174.2, R1A43.P$1, R219.1
unnamed: C175.2, R2A43.P$1, R220.1
unnamed: C178.1, JP268.2, SJ45.1
unnamed: LED45.A, R223.1
unnamed: Q45.1, R222.2
unnamed: LED45.C, Q45.3
unnamed: C178.2, R1A44.P$1, R224.1
unnamed: C179.2, R2A44.P$1, R225.1
unnamed: C182.1, JP274.2, SJ46.1
unnamed: LED46.A, R228.1
unnamed: Q46.1, R227.2
unnamed: LED46.C, Q46.3
unnamed: C182.2, R1A45.P$1, R229.1
unnamed: C183.2, R2A45.P$1, R230.1
unnamed: C186.1, JP280.2, SJ47.1
unnamed: LED47.A, R233.1
unnamed: Q47.1, R232.2
unnamed: LED47.C, Q47.3
unnamed: C186.2, R1A46.P$1, R234.1
unnamed: C187.2, R2A46.P$1, R235.1
unnamed: C190.1, JP286.2, SJ48.1
unnamed: LED48.A, R238.1
unnamed: Q48.1, R237.2
unnamed: LED48.C, Q48.3
unnamed: C190.2, R1A47.P$1, R239.1
unnamed: C191.2, R2A47.P$1, R240.1
unnamed: C194.1, JP292.2, SJ49.1
unnamed: LED49.A, R243.1
unnamed: Q49.1, R242.2
unnamed: LED49.C, Q49.3
unnamed: C194.2, R1A48.P$1, R244.1
unnamed: C195.2, R2A48.P$1, R245.1
unnamed: C198.1, JP298.2, SJ50.1
unnamed: LED50.A, R248.1
unnamed: Q50.1, R247.2
unnamed: LED50.C, Q50.3
unnamed: C198.2, R1A49.P$1, R249.1
unnamed: C199.2, R2A49.P$1, R250.1
unnamed: C202.1, JP304.2, SJ51.1
unnamed: LED51.A, R253.1
unnamed: Q51.1, R252.2
unnamed: LED51.C, Q51.3
unnamed: C202.2, R1A50.P$1, R254.1
unnamed: C203.2, R2A50.P$1, R255.1
unnamed: C206.1, JP310.2, SJ52.1
unnamed: LED52.A, R258.1
unnamed: Q52.1, R257.2
unnamed: LED52.C, Q52.3
unnamed: C206.2, R1A51.P$1, R259.1
unnamed: C207.2, R2A51.P$1, R260.1
unnamed: C210.1, JP316.2, SJ53.1
unnamed: LED53.A, R263.1
unnamed: Q53.1, R262.2
unnamed: LED53.C, Q53.3
unnamed: C210.2, R1A52.P$1, R264.1
unnamed: C211.2, R2A52.P$1, R265.1
unnamed: C214.1, JP322.2, SJ54.1
unnamed: LED54.A, R268.1
unnamed: Q54.1, R267.2
unnamed: LED54.C, Q54.3
unnamed: C214.2, R1A53.P$1, R269.1
unnamed: C215.2, R2A53.P$1, R270.1
unnamed: C218.1, JP328.2, SJ55.1
unnamed: LED55.A, R273.1
unnamed: Q55.1, R272.2
unnamed: LED55.C, Q55.3
unnamed: C218.2, R1A54.P$1, R274.1
unnamed: C219.2, R2A54.P$1, R275.1
unnamed: C222.1, JP334.2, SJ56.1
unnamed: LED56.A, R278.1
unnamed: Q56.1, R277.2
unnamed: LED56.C, Q56.3
unnamed: C222.2, R1A55.P$1, R279.1
unnamed: C223.2, R2A55.P$1, R280.1
unnamed: C226.1, JP340.2, SJ57.1
unnamed: LED57.A, R283.1
unnamed: Q57.1, R282.2
unnamed: LED57.C, Q57.3
unnamed: C226.2, R1A56.P$1, R284.1
unnamed: C227.2, R2A56.P$1, R285.1
unnamed: C230.1, JP346.2, SJ58.1
unnamed: LED58.A, R288.1
unnamed: Q58.1, R287.2
unnamed: LED58.C, Q58.3
unnamed: C230.2, R1A57.P$1, R289.1
unnamed: C231.2, R2A57.P$1, R290.1
unnamed: C234.1, JP352.2, SJ59.1
unnamed: LED59.A, R293.1
unnamed: Q59.1, R292.2
unnamed: LED59.C, Q59.3
unnamed: C234.2, R1A58.P$1, R294.1
unnamed: C235.2, R2A58.P$1, R295.1
unnamed: C238.1, JP358.2, SJ60.1
unnamed: LED60.A, R298.1
unnamed: Q60.1, R297.2
unnamed: LED60.C, Q60.3
unnamed: C238.2, R1A59.P$1, R299.1
unnamed: C239.2, R2A59.P$1, R300.1
OUT+: JP3.1, U1.5
OUT+1: JP8.1, U2.5
OUT+2: JP14.1, U3.5
OUT+3: JP20.1, U4.5
OUT+4: JP26.1, U5.5
OUT+5: JP32.1, U6.5
OUT+6: JP38.1, U7.5
OUT+7: JP44.1, U8.5
OUT+8: JP50.1, U9.5
OUT+9: JP56.1, U10.5
OUT+10: JP62.1, U11.5
OUT+11: JP68.1, U12.5
OUT+12: JP74.1, U13.5
OUT+13: JP80.1, U14.5
OUT+14: JP86.1, U15.5
OUT+15: JP92.1, U16.5
OUT+16: JP98.1, U17.5
OUT+17: JP104.1, U18.5
OUT+18: JP110.1, U19.5
OUT+19: JP116.1, U20.5
OUT+20: JP122.1, U21.5
OUT+21: JP128.1, U22.5
OUT+22: JP134.1, U23.5
OUT+23: JP140.1, U24.5
OUT+24: JP146.1, U25.5
OUT+25: JP152.1, U26.5
OUT+26: JP158.1, U27.5
OUT+27: JP164.1, U28.5
OUT+28: JP170.1, U29.5
OUT+29: JP176.1, U30.5
OUT+30: JP182.1, U31.5
OUT+31: JP188.1, U32.5
OUT+32: JP194.1, U33.5
OUT+33: JP200.1, U34.5
OUT+34: JP206.1, U35.5
OUT+35: JP212.1, U36.5
OUT+36: JP218.1, U37.5
OUT+37: JP224.1, U38.5
OUT+38: JP230.1, U39.5
OUT+39: JP236.1, U40.5
OUT+40: JP242.1, U41.5
OUT+41: JP248.1, U42.5
OUT+42: JP254.1, U43.5
OUT+43: JP260.1, U44.5
OUT+44: JP266.1, U45.5
OUT+45: JP272.1, U46.5
OUT+46: JP278.1, U47.5
OUT+47: JP284.1, U48.5
OUT+48: JP290.1, U49.5
OUT+49: JP296.1, U50.5
OUT+50: JP302.1, U51.5
OUT+51: JP308.1, U52.5
OUT+52: JP314.1, U53.5
OUT+53: JP320.1, U54.5
OUT+54: JP326.1, U55.5
OUT+55: JP332.1, U56.5
OUT+56: JP338.1, U57.5
OUT+57: JP344.1, U58.5
OUT+58: JP350.1, U59.5
OUT+59: JP356.1, U60.5
OUT-: JP3.2, U1.8
OUT-1: JP8.2, U2.8
OUT-2: JP14.2, U3.8
OUT-3: JP20.2, U4.8
OUT-4: JP26.2, U5.8
OUT-5: JP32.2, U6.8
OUT-6: JP38.2, U7.8
OUT-7: JP44.2, U8.8
OUT-8: JP50.2, U9.8
OUT-9: JP56.2, U10.8
OUT-10: JP62.2, U11.8
OUT-11: JP68.2, U12.8
OUT-12: JP74.2, U13.8
OUT-13: JP80.2, U14.8
OUT-14: JP86.2, U15.8
OUT-15: JP92.2, U16.8
OUT-16: JP98.2, U17.8
OUT-17: JP104.2, U18.8
OUT-18: JP110.2, U19.8
OUT-19: JP116.2, U20.8
OUT-20: JP122.2, U21.8
OUT-21: JP128.2, U22.8
OUT-22: JP134.2, U23.8
OUT-23: JP140.2, U24.8
OUT-24: JP146.2, U25.8
OUT-25: JP152.2, U26.8
OUT-26: JP158.2, U27.8
OUT-27: JP164.2, U28.8
OUT-28: JP170.2, U29.8
OUT-29: JP176.2, U30.8
OUT-30: JP182.2, U31.8
OUT-31: JP188.2, U32.8
OUT-32: JP194.2, U33.8
OUT-33: JP200.2, U34.8
OUT-34: JP206.2, U35.8
OUT-35: JP212.2, U36.8
OUT-36: JP218.2, U37.8
OUT-37: JP224.2, U38.8
OUT-38: JP230.2, U39.8
OUT-39: JP236.2, U40.8
OUT-40: JP242.2, U41.8
OUT-41: JP248.2, U42.8
OUT-42: JP254.2, U43.8
OUT-43: JP260.2, U44.8
OUT-44: JP266.2, U45.8
OUT-45: JP272.2, U46.8
OUT-46: JP278.2, U47.8
OUT-47: JP284.2, U48.8
OUT-48: JP290.2, U49.8
OUT-49: JP296.2, U50.8
OUT-50: JP302.2, U51.8
OUT-51: JP308.2, U52.8
OUT-52: JP314.2, U53.8
OUT-53: JP320.2, U54.8
OUT-54: JP326.2, U55.8
OUT-55: JP332.2, U56.8
OUT-56: JP338.2, U57.8
OUT-57: JP344.2, U58.8
OUT-58: JP350.2, U59.8
OUT-59: JP356.2, U60.8
SDN*: JP1.1, R3.1, R5.1, U1.1
SDN*1: JP9.1, R6.1, R7.1, U2.1
SDN*2: JP15.1, R11.1, R12.1, U3.1
SDN*3: JP21.1, R16.1, R17.1, U4.1
SDN*4: JP27.1, R21.1, R22.1, U5.1
SDN*5: JP33.1, R26.1, R27.1, U6.1
SDN*6: JP39.1, R31.1, R32.1, U7.1
SDN*7: JP45.1, R36.1, R37.1, U8.1
SDN*8: JP51.1, R41.1, R42.1, U9.1
SDN*9: JP57.1, R46.1, R47.1, U10.1
SDN*10: JP63.1, R51.1, R52.1, U11.1
SDN*11: JP69.1, R56.1, R57.1, U12.1
SDN*12: JP75.1, R61.1, R62.1, U13.1
SDN*13: JP81.1, R66.1, R67.1, U14.1
SDN*14: JP87.1, R71.1, R72.1, U15.1
SDN*15: JP93.1, R76.1, R77.1, U16.1
SDN*16: JP99.1, R81.1, R82.1, U17.1
SDN*17: JP105.1, R86.1, R87.1, U18.1
SDN*18: JP111.1, R91.1, R92.1, U19.1
SDN*19: JP117.1, R96.1, R97.1, U20.1
SDN*20: JP123.1, R101.1, R102.1, U21.1
SDN*21: JP129.1, R106.1, R107.1, U22.1
SDN*22: JP135.1, R111.1, R112.1, U23.1
SDN*23: JP141.1, R116.1, R117.1, U24.1
SDN*24: JP147.1, R121.1, R122.1, U25.1
SDN*25: JP153.1, R126.1, R127.1, U26.1
SDN*26: JP159.1, R131.1, R132.1, U27.1
SDN*27: JP165.1, R136.1, R137.1, U28.1
SDN*28: JP171.1, R141.1, R142.1, U29.1
SDN*29: JP177.1, R146.1, R147.1, U30.1
SDN*30: JP183.1, R151.1, R152.1, U31.1
SDN*31: JP189.1, R156.1, R157.1, U32.1
SDN*32: JP195.1, R161.1, R162.1, U33.1
SDN*33: JP201.1, R166.1, R167.1, U34.1
SDN*34: JP207.1, R171.1, R172.1, U35.1
SDN*35: JP213.1, R176.1, R177.1, U36.1
SDN*36: JP219.1, R181.1, R182.1, U37.1
SDN*37: JP225.1, R186.1, R187.1, U38.1
SDN*38: JP231.1, R191.1, R192.1, U39.1
SDN*39: JP237.1, R196.1, R197.1, U40.1
SDN*40: JP243.1, R201.1, R202.1, U41.1
SDN*41: JP249.1, R206.1, R207.1, U42.1
SDN*42: JP255.1, R211.1, R212.1, U43.1
SDN*43: JP261.1, R216.1, R217.1, U44.1
SDN*44: JP267.1, R221.1, R222.1, U45.1
SDN*45: JP273.1, R226.1, R227.1, U46.1
SDN*46: JP279.1, R231.1, R232.1, U47.1
SDN*47: JP285.1, R236.1, R237.1, U48.1
SDN*48: JP291.1, R241.1, R242.1, U49.1
SDN*49: JP297.1, R246.1, R247.1, U50.1
SDN*50: JP303.1, R251.1, R252.1, U51.1
SDN*51: JP309.1, R256.1, R257.1, U52.1
SDN*52: JP315.1, R261.1, R262.1, U53.1
SDN*53: JP321.1, R266.1, R267.1, U54.1
SDN*54: JP327.1, R271.1, R272.1, U55.1
SDN*55: JP333.1, R276.1, R277.1, U56.1
SDN*56: JP339.1, R281.1, R282.1, U57.1
SDN*57: JP345.1, R286.1, R287.1, U58.1
SDN*58: JP351.1, R291.1, R292.1, U59.1
SDN*59: JP357.1, R296.1, R297.1, U60.1
VCC: C1.1, C2.1, JP1.2, R4.2, R5.2, U1.6
VCC1: C5.1, C8.1, JP9.2, R6.2, R8.2, U2.6
VCC2: C9.1, C12.1, JP15.2, R11.2, R13.2, U3.6
VCC3: C13.1, C16.1, JP21.2, R16.2, R18.2, U4.6
VCC4: C17.1, C20.1, JP27.2, R21.2, R23.2, U5.6
VCC5: C21.1, C24.1, JP33.2, R26.2, R28.2, U6.6
VCC6: C25.1, C28.1, JP39.2, R31.2, R33.2, U7.6
VCC7: C29.1, C32.1, JP45.2, R36.2, R38.2, U8.6
VCC8: C33.1, C36.1, JP51.2, R41.2, R43.2, U9.6
VCC9: C37.1, C40.1, JP57.2, R46.2, R48.2, U10.6
VCC10: C41.1, C44.1, JP63.2, R51.2, R53.2, U11.6
VCC11: C45.1, C48.1, JP69.2, R56.2, R58.2, U12.6
VCC12: C49.1, C52.1, JP75.2, R61.2, R63.2, U13.6
VCC13: C53.1, C56.1, JP81.2, R66.2, R68.2, U14.6
VCC14: C57.1, C60.1, JP87.2, R71.2, R73.2, U15.6
VCC15: C61.1, C64.1, JP93.2, R76.2, R78.2, U16.6
VCC16: C65.1, C68.1, JP99.2, R81.2, R83.2, U17.6
VCC17: C69.1, C72.1, JP105.2, R86.2, R88.2, U18.6
VCC18: C73.1, C76.1, JP111.2, R91.2, R93.2, U19.6
VCC19: C77.1, C80.1, JP117.2, R96.2, R98.2, U20.6
VCC20: C81.1, C84.1, JP123.2, R101.2, R103.2, U21.6
VCC21: C85.1, C88.1, JP129.2, R106.2, R108.2, U22.6
VCC22: C89.1, C92.1, JP135.2, R111.2, R113.2, U23.6
VCC23: C93.1, C96.1, JP141.2, R116.2, R118.2, U24.6
VCC24: C97.1, C100.1, JP147.2, R121.2, R123.2, U25.6
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
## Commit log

2015-05-01 Adding hardware files, updating README
2015-10-16 new v11 panel
